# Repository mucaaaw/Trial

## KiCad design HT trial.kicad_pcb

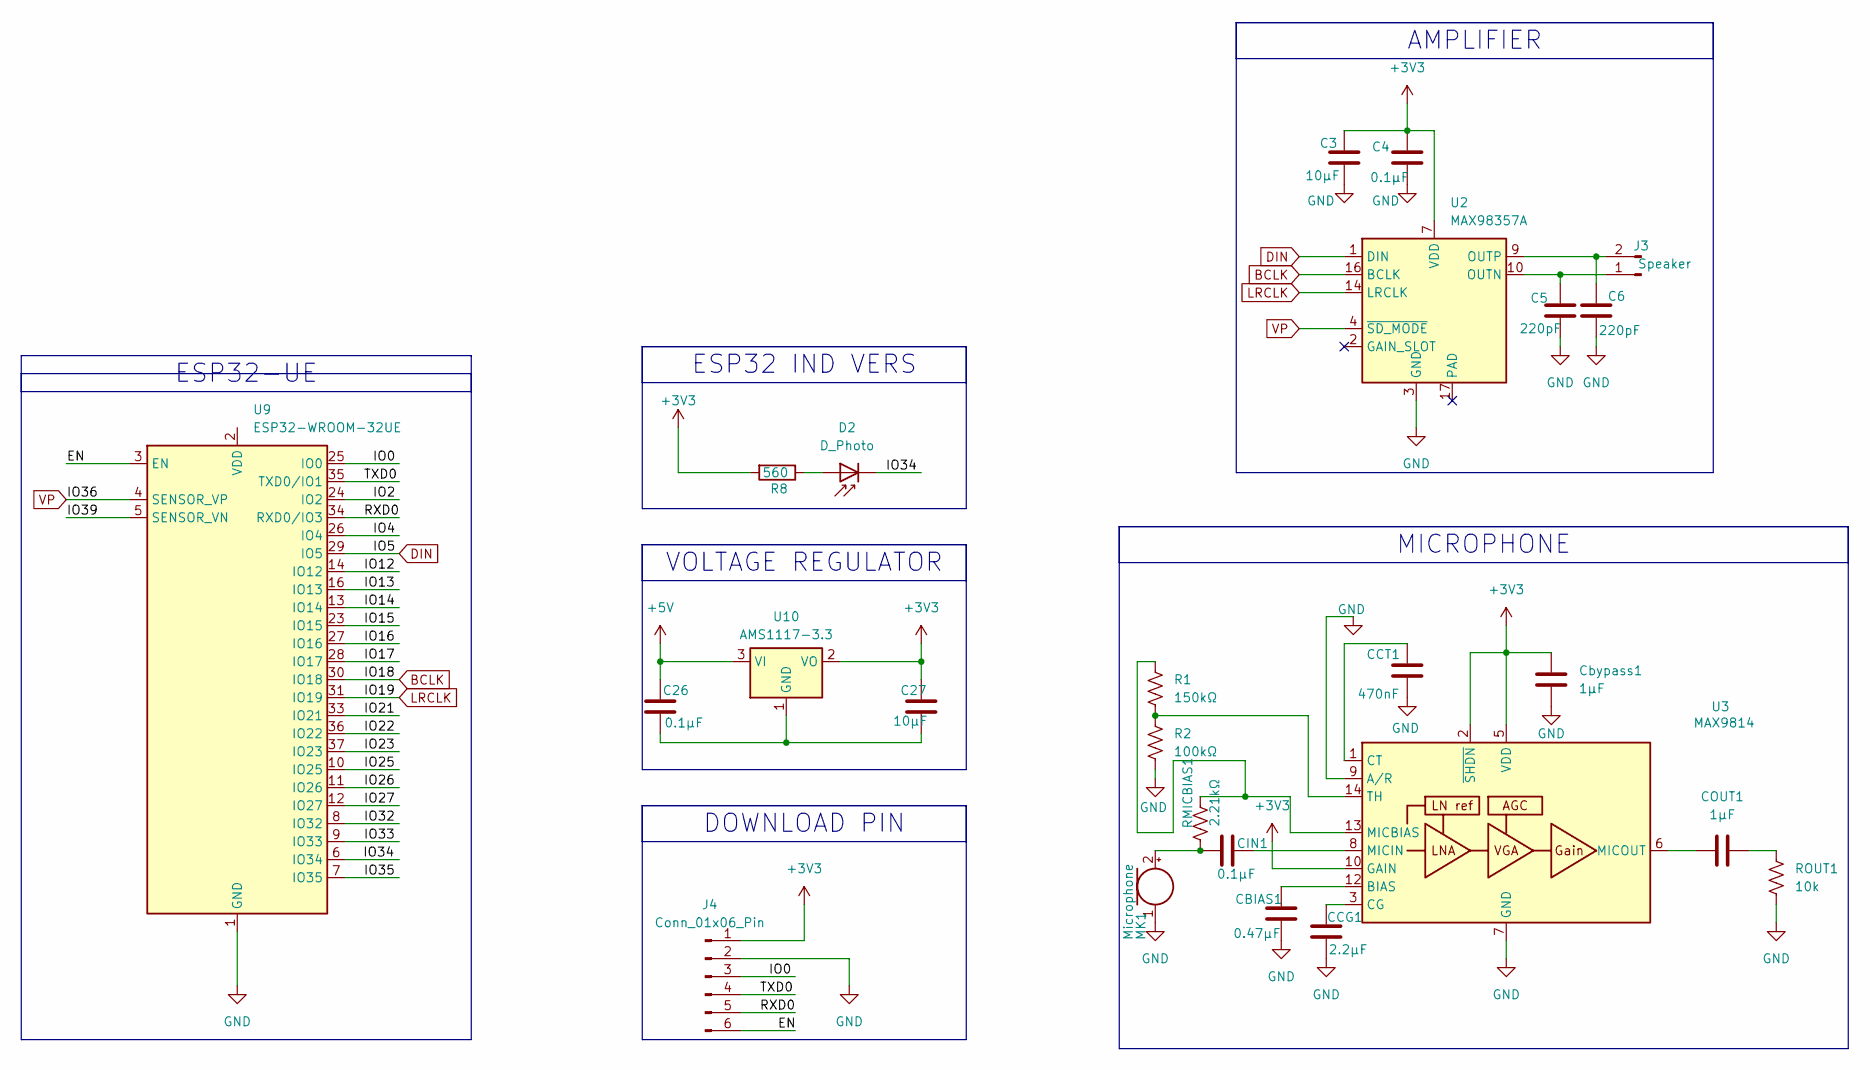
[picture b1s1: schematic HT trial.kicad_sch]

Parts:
C3: 10µF; C_0201_0603Metric_Pad0.64x0.40mm_HandSolder
C4: 0.1µF; C_0201_0603Metric_Pad0.64x0.40mm_HandSolder
C5, C6: 220pF; C_0201_0603Metric_Pad0.64x0.40mm_HandSolder
C26: 0.1µF; C_0201_0603Metric
C27: 10µF; C_0201_0603Metric
CBIAS1: 0.47µF; C_0201_0603Metric_Pad0.64x0.40mm_HandSolder
CCG1: 2.2µF; C_0201_0603Metric_Pad0.64x0.40mm_HandSolder
CCT1: 470nF; C_0201_0603Metric_Pad0.64x0.40mm_HandSolder
CIN1: 0.1µF; C_0201_0603Metric_Pad0.64x0.40mm_HandSolder
COUT1: 1µF; C_0201_0603Metric_Pad0.64x0.40mm_HandSolder
Cbypass1: 1µF; C_0201_0603Metric_Pad0.64x0.40mm_HandSolder
D2: D_Photo; D_SOD-123F
J3: Speaker; JST_VH_B2P-VH-B_1x02_P3.96mm_Vertical
J4: Conn_01x06_Pin; JST_EH_B6B-EH-A_1x06_P2.50mm_Vertical
MK1: Microphone; POM-2244P-C3310-2-R
R1: 150kΩ; R_0201_0603Metric
R2: 100kΩ; R_0201_0603Metric
R8: 560; R_0201_0603Metric_Pad0.64x0.40mm_HandSolder
RMICBIAS1: 2.21kΩ; R_0201_0603Metric
ROUT1: 10k; R_0603_1608Metric_Pad0.98x0.95mm_HandSolder
U2: MAX98357A; TQFN-16-1EP_3x3mm_P0.5mm_EP1.23x1.23mm
U3: MAX9814; DFN-14-1EP_3x3mm_P0.4mm_EP1.78x2.35mm
U9: ESP32-WROOM-32UE
U10: AMS1117-3.3; SOT-223-3_TabPin2

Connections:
+3V3: C3.1, C4.1, C27.1, Cbypass1.1, J4.1, R8.2, U2.7 (VDD), U2.8 (VDD), U3.2 (~SHDN), U3.5 (VDD), U3.10 (GAIN), U10.2 (VO)
+5V: C26.1, U10.3 (VI)
/EN: J4.6, U9.3 (EN)
/IO0: J4.3, U9.25 (IO0)
/IO2: U9.24 (IO2)
/IO4: U9.26 (IO4)
/IO12: U9.14 (IO12)
/IO13: U9.16 (IO13)
/IO14: U9.13 (IO14)
/IO15: U9.23 (IO15)
/IO16: U9.27 (IO16)
/IO17: U9.28 (IO17)
/IO21: U9.33 (IO21)
/IO22: U9.36 (IO22)
/IO23: U9.37 (IO23)
/IO25: U9.10 (IO25)
/IO26: U9.11 (IO26)
/IO27: U9.12 (IO27)
/IO32: U9.8 (IO32)
/IO33: U9.9 (IO33)
/IO34: D2.1 (K), U9.6 (IO34)
/IO35: U9.7 (IO35)
/IO39: U9.5 (SENSOR_VN)
/RXD0: J4.5, U9.34 (RXD0/IO3)
/TXD0: J4.4, U9.35 (TXD0/IO1)
BCLK: U2.16 (BCLK), U9.30 (IO18)
DIN: U2.1 (DIN), U9.29 (IO5)
GND: C3.2, C4.2, C5.2, C6.2, CBIAS1.2, CCG1.2, CCT1.2, Cbypass1.2, J4.2, MK1.1 (-), R2.2, ROUT1.2, U2.3 (GND), U2.11 (GND), U2.15 (GND), U3.4 (GND), U3.7 (GND), U3.9 (A/R), U3.11 (GND), U3.15 (GND), U9.1 (GND), U9.15 (GND), U9.38 (GND), U9.39 (GND)
LRCLK: U2.14 (LRCLK), U9.31 (IO19)
unnamed: COUT1.2, ROUT1.1
unnamed: D2.2 (A), R8.1
unnamed: C5.1, J3.1, U2.10 (OUTN)
unnamed: C6.1, J3.2, U2.9 (OUTP)
unnamed: CIN1.1, MK1.2 (+), RMICBIAS1.2
unnamed: CBIAS1.1, U3.12 (BIAS)
unnamed: CCG1.1, U3.3 (CG)
unnamed: CCT1.1, U3.1 (CT)
unnamed: R1.1, RMICBIAS1.1, U3.13 (MICBIAS)
unnamed: CIN1.2, U3.8 (MICIN)
unnamed: COUT1.1, U3.6 (MICOUT)
unnamed: R1.2, R2.1, U3.14 (TH)
unnamed: C26.2, C27.2, U10.1 (GND)
VP: U2.4 (~SD_MODE), U9.4 (SENSOR_VP)

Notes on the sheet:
AMPLIFIER
DOWNLOAD PIN
ESP32-UE
MICROPHONE
VOLTAGE REGULATOR
ESP32 IND VERS

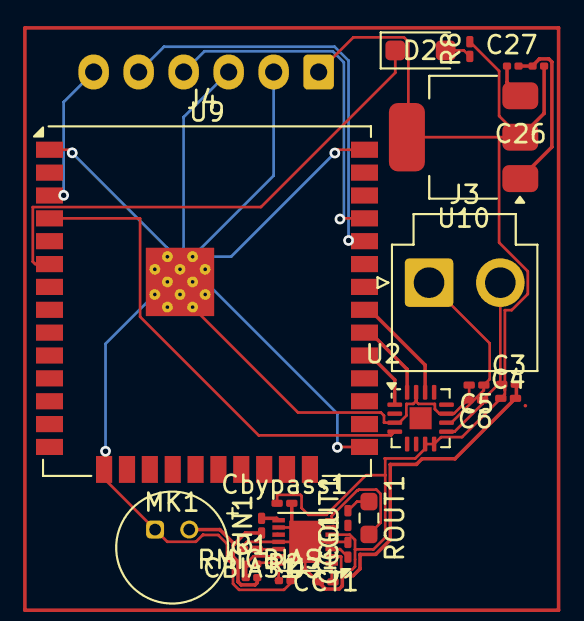
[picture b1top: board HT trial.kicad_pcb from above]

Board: 2 copper layers, 25 parts (1 on the bottom side), 25 nets.
